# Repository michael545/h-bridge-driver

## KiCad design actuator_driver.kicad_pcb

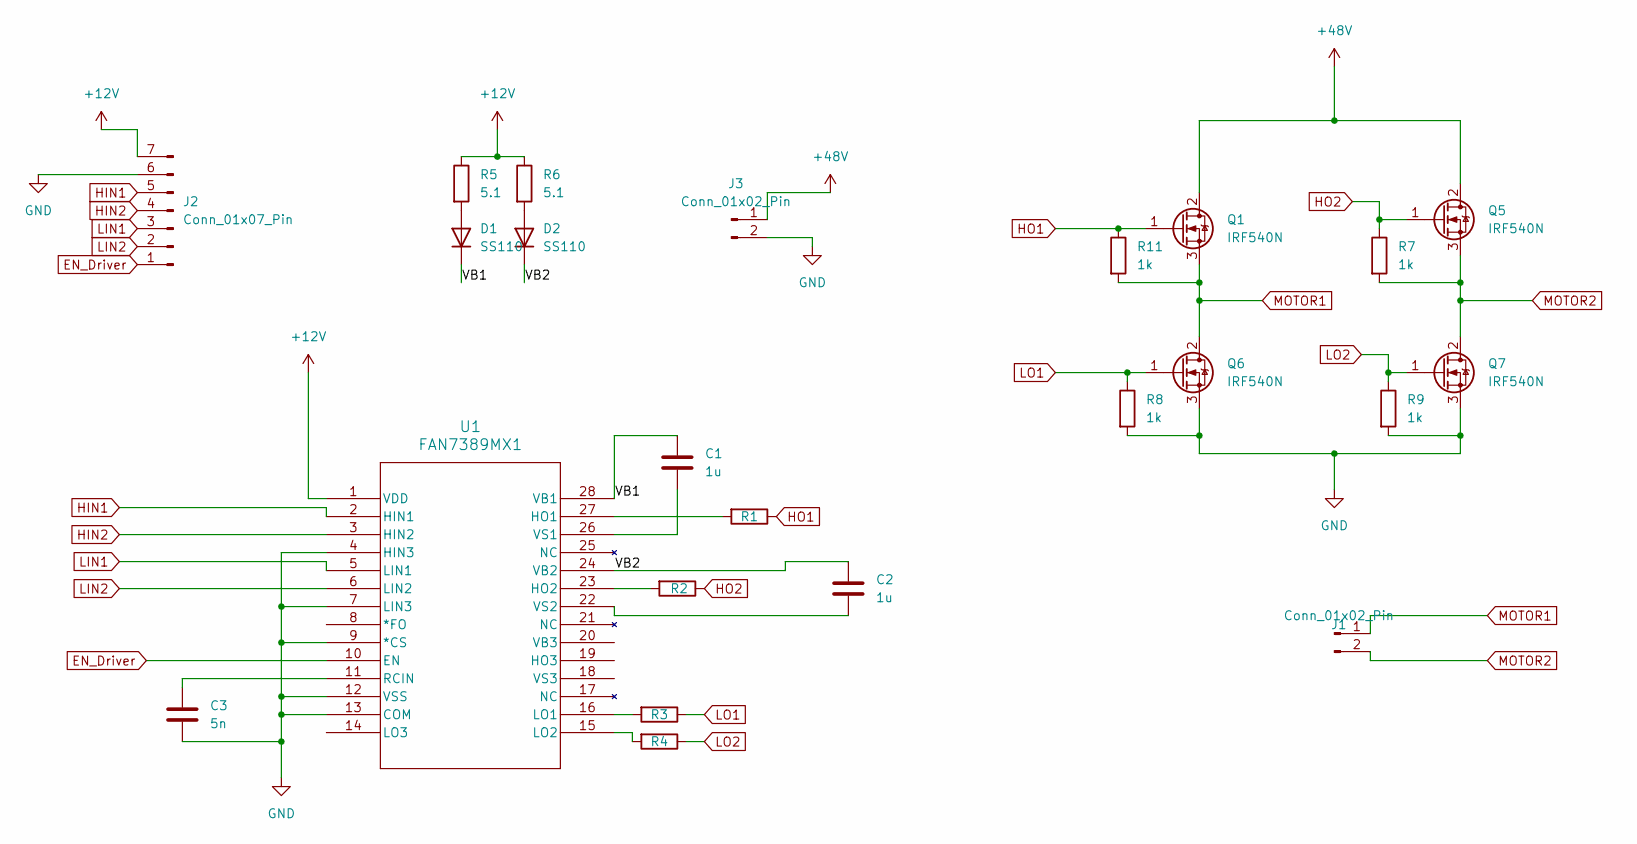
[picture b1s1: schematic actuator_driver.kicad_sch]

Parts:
C1, C2: 1u; C_1210_3225Metric
C3: 5n; C_1206_3216Metric_Pad1.33x1.80mm_HandSolder
D1, D2: SS110; D_SMA
J1: Conn_01x02_Pin; AMASS_XT60IPW-M_1x03_P7.20mm_Horizontal
J2: Conn_01x07_Pin; JST_EH_B7B-EH-A_1x07_P2.50mm_Vertical
J3: Conn_01x02_Pin; TerminalBlock_WAGO_236-102_1x02_P5.00mm_45Degree
Q1, Q5, Q6, Q7: IRF540N; TO-263-2
R1, R2, R3, R4: 10; R_1206_3216Metric_Pad1.30x1.75mm_HandSolder
R5, R6: 5.1; R_1206_3216Metric_Pad1.30x1.75mm_HandSolder
R7, R8, R9, R11: 1k; R_1206_3216Metric_Pad1.30x1.75mm_HandSolder
U1: FAN7389MX1; SOIC-28W_7.5x17.9mm_P1.27mm

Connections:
+12V: J2.7, R5.1, R6.1, U1.1 (VDD)
+48V: J3.1, Q1.2 (D), Q5.2 (D)
/VB1: C1.1, D1.1 (K), U1.28 (VB1)
/VB2: C2.1, D2.1 (K), U1.24 (VB2)
EN_Driver: J2.1, U1.10 (EN)
GND: C3.2, J2.6, J3.2, Q6.3 (S), Q7.3 (S), R8.2, R9.2, U1.4 (HIN3), U1.7 (LIN3), U1.9 (*CS), U1.12 (VSS), U1.13 (COM)
HIN1: J2.5, U1.2 (HIN1)
HIN2: J2.4, U1.3 (HIN2)
HO1: Q1.1 (G), R1.1, R11.1
HO2: Q5.1 (G), R2.1, R7.1
LIN1: J2.3, U1.5 (LIN1)
LIN2: J2.2, U1.6 (LIN2)
LO1: Q6.1 (G), R3.1, R8.1
LO2: Q7.1 (G), R4.1, R9.1
MOTOR1: J1.1, Q1.3 (S), Q6.2 (D), R11.2
MOTOR2: J1.2, Q5.3 (S), Q7.2 (D), R7.2
unnamed: D1.2 (A), R5.2
unnamed: D2.2 (A), R6.2
unnamed: R1.2, U1.27 (HO1)
unnamed: R2.2, U1.23 (HO2)
unnamed: R3.2, U1.16 (LO1)
unnamed: R4.2, U1.15 (LO2)
unnamed: C3.1, U1.11 (RCIN)
unnamed: C1.2, U1.26 (VS1)
unnamed: C2.2, U1.22 (VS2)

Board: 2 copper layers, 23 parts (0 on the bottom side), 25 nets, no tracks yet.

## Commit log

2025-09-30 new label
2025-09-30 new footprints
2025-09-30 new XT60 connector
2025-10-01 latest schematic
2025-10-01 jitthi takeover
2025-10-01 jitthin takeover
2025-10-01 autosave
2025-10-01 autosave test
2025-10-01 other comp
2025-10-01 connector update
